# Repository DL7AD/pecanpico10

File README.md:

# Pecan Pico 10 - A lightweight APRS tracker and digipeater
This project contains the Pecan Pico project in it's 10th version. A Pecan is a cheap lightweight APRS position tracker designed especially for small ballons which may fly for months. This tracker has been made in respect of weight, functionality and price because it's usually used once like a satellite. While the balloon can fly for a long time, this tracker is solar powered and recharges it's battery at daytime and uses the power stored in the battery at night.
Since this version the tracker is also able to receive APRS (AFSK and FSK). So it's able to operate as solar enabled digipeater.

The main features are:
- GPS Tracking
- Taking pictures
- APRS receiption and transmission
- Measuring Temperature/Airpressure/Humidity (up to 3 separate sensors)
- Digipeating

__Powering:__ The Pecan Pico 10 can be powered either by USB or by a single LiPO cell which are charged with solar cells. In power safe mode, it uses 50mW and around 150-200mW in normal operation. [dive deeper](powering.md)

__Storage:__ There can be stored up to 14,560 data points (GPS & telemetry) without any external memory devices. For additional storage and picture logging, a Micro SD card can be inserted into the device.

__Transceiver:__ Though the software is mainly optimized for APRS operation, it can be also used for 2/4FSK (RTTY) and OOK (CW) operation. The maximum transmission power is 100mW. While the transceiver has ony a signle LPF, it is only able to operate on one frequency band (either 2m or 70cm). The inductors/capacitors in the schematic are adjusted to the 2m amateur radio band, but with different components it can be used on the 70cm band too. The fastest tested 2FSK transmission speed is 115k2. While the Pecan can transmit AFSK and 2FSK, it is only able to receive AFSK APRS. It is possible to receive 2FSK APRS too, although the software hasn't been implemented yet.

__Image transmission:__ The software makes use of the JPEG compression of the Omnivision OV5640. Although the connector is suitable for some other cameras too, the OV5640 is the only camera which can be used due to the missing HREF pin. The protocol being used for the images transmission is APRS/SSDV. This protocol is fully APRS compatible but needs extra software to be decoded again which is included in this project. Though the camera can do pictures up to 5MP, there is only enough memory available to take XGA pictures (1024x768px).
TODO: Precise description about APRS/SSDV

__Telemetry transmission:__ Since APRS does only allow a ceirtain amount of telemetry fields being transmitted, the complete telemetry is sent as a binary format along with the position transmissions in the comment field. The APRS packet stays completly compatible with the existing network. The additional telemetry can be decoded with an additional decoder which is included in this project. It is the same decoder  which decodes APRS/SSDV too. The software is currently running on [this website](http://www.wlankabel.com).

__Sensors:__ The Pecan uses a single chip (BME280) to measure the temperature, airpressure and humidity. There can be attached up to two additional BME280's for various purposes like internal and external temperatures. You may want to have an external sensor while the internal sensor on the PCB is influenced by the heat generated by the components. The difference can vary between 2 and 10°C.

__Additional sensors:__ The Pecan provides an external busses (I2C and UART) from where addional sensors can be accessed. On the 10a variant is a signle GPIO pin, which can be used for varios stuff. There can either be I2C or UART be used on the 10a variant while I2C shared the same pins as UART does. In the 10b variant the additional GPIO pin has been removed, therefore I2C and UART are now separate. If you have no need for UART/I2C, those pins can be also used as normal GPIO's.

__GNSS (GPS):__ The ublox EVA-7M chip can receive GPS which is used to determine it's location and the region specific APRS frequency. Since the GPS draws a lot of power, it can be switched on and off as needed. The device is also compatible with the ublox EVA-M8 which can receive GLONASS, Beido and Galileo too.

__Debugging/Configuration:__ The device can be accessed over USB (serial terminal) in order to configure it or get debug messages out of the device. The log memory can also be accessed over USB.

__Schematic:__ Here we go! [Download](https://raw.githubusercontent.com/DL7AD/pecanpico10/master/tracker/hardware/pico/output/pecanpico10.pdf)

__Operation variants__
- Car/Balloon Tracker
- Digipeater
- Weather station (software not implemented yet)
- Image transmitting device
All variants can be combined with each other

__Software Manual__
TODO: How to access it through USB
TODO: How to configure the device

__More:__ *Flashing the chip (link missing)*

# Transmitted test pictures

<br>
*Closed Airport Berlin Tempelhof roughly 3km altitude*

<br>
*Picture at low altitude right away after the launch*

<br>
*Clouds somewhere in Germany at an altitude of 12km*

<br>
*Lakes in East Poland (Myślibórz) at 8km altitude, antenna and radar reflector in the picture*

<br>
*South East Berlin (Adlershof/Grünau) taken at roughly 5km altitude*

<br>
*Launch with solar heated balloons (a cooperation with [Aerocene](http://www.aerocene.org))*

Contributions
=============

Please let me know if you have questions or ideas: sven.steudte@gmail.com

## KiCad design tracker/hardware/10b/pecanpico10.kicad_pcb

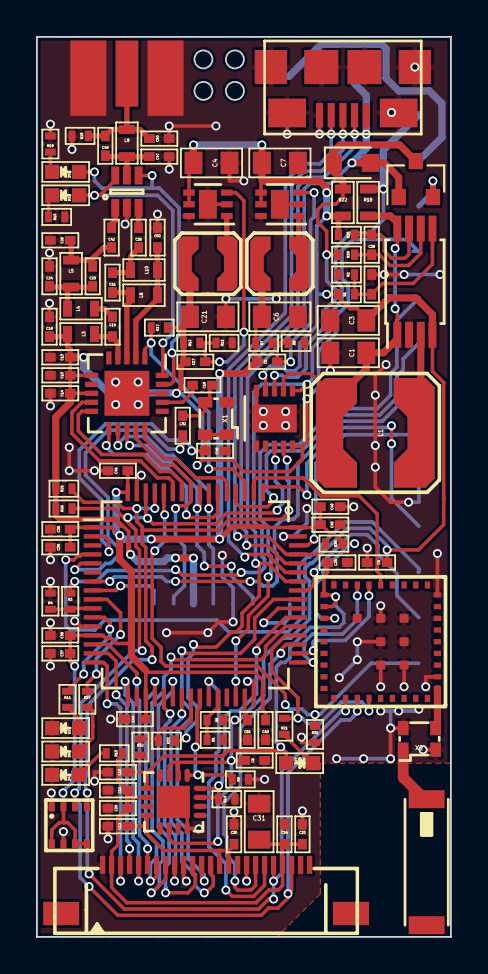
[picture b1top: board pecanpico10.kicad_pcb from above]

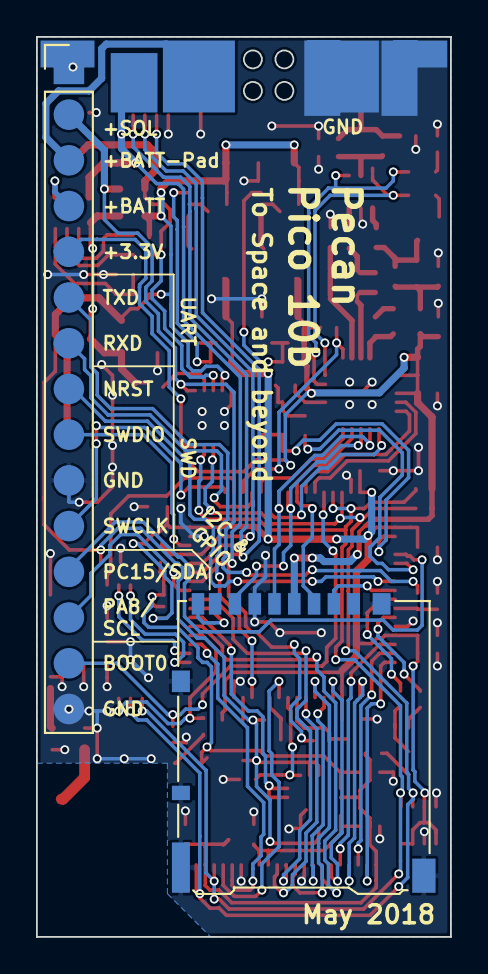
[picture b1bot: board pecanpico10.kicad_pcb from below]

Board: 2 copper layers, 23.0 x 50.0 mm, 119 parts (7 on the bottom side), 93 nets.

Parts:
AE1: 1575AT43A0040E; 575AT43A40
C1, C31: 22u; C_0805
C2: 1n; C_0402
C3, C4, C6, C7, C21: 10u; C_0805
C5, C17, C24, C47, C50: 22p; C_0402
C8, C9, C10, C11, C12, C13, C37, C39, C40, C51: 2u2; C_0402
C14, C20, C29, C30, C33, C35, C43, C44, C45, C46, C48: 100n; C_0402
C15, C16, C34: 100p; C_0402
C18, C19, C36, C42: 470p; C_0402
C25: 3.3p; C_0402
C26: 15p; C_0402
C28: 1u; C_0402
C32, C38: 10n; C_0402
C41: 6.2p; C_0402
C49: 2.2p; C_0402
C52: 12p; C_0402
D1: SDM100K30L-7; D_SOD-323
D2, D7: red; LED_0603
D3, D5: green; LED_0603
D4: yellow; LED_0603
D6: blue; LED_0603
IC1: SPV1040T; TSSOP-8_4.4x3mm_Pitch0.65mm
IC2, IC8: TPS62260DRVR; DFN-6-1EP_2x2mm_Pitch0.65mm
IC3: ADP322ACPZ-115-R7; QFN-16-1EP_3x3mm_Pitch0.5mm
IC4: Si4464-B1B-FM; QFN-20-1EP_4x4mm_Pitch0.5mm
IC5: STM32F413RHT6; LQFP-64_10x10mm_Pitch0.5mm
IC6: EVA-7M or EVA-M8; EVA7M
IC7: PAC1720-1-AIA-TR; DFN-10-1EP_3x3mm_Pitch0.5mm
IC9: BME280
IC10: AS213-92LF; SC-70-6
J1: DM3AT-SF-PEJM5; Hirose_DM3AT-SF-PEJM5
J2: CONN_01X15; Pin_Header_Straight_1x15_Pitch2.54mm
L1: LPS6225-103; LPS6225
L2, L7: LPS3015-222; LPS3015
L3: 470n; R_0603
L4, L9: 56n; R_0603
L5: 82n; R_0603
L8: 220n; R_0603
L10: 150n; R_0603
P1: CONN_01X25; FFC1x24_0.5mm
P3: ZX62-B-5PA(33); USB_Micro-B_SMD
P4: SMA; SMA_EDGE
Q1: FDN306P; SOT-23
R1: 220k; R_0402
R2, R8, R13, R17, R31: 100k; R_0402
R3, R5, R33: 22k; R_0402
R4, R6, R9, R14, R32: 10k; R_0402
R7: 402k; R_0402
R10, R15, R19, R21, R27, R35: 1k5; R_0402
R11, R29, R30: 1k; R_0402
R12: 470k; R_0402
R18, R22: 0R1; R_0603
R20: 1M; R_0402
R25, R26: 4k7; R_0402
W1, W11: Pad; PAD_3x3
W2, W3: Testpad; PAD_3x1.5
W10: Pad; PAD_6x3
X1: KT2016K26000BCW18ZAS; tcxo
X2: SF2316H; tcxo

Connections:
+1V8: C12.1, C30.2, IC3.8, P1.14, P1.15
+3V0: C5.1, C6.1, C35.2, C37.1, C38.1, C39.2, C40.2, C43.2, C44.2, C45.2, C46.2, IC5.1, IC5.13, IC5.19, IC5.32, IC5.48, IC5.64, IC6.21, IC9.2, IC9.5, IC9.6, IC9.8, L2.1, R7.1, R35.1
+3V3: C13.1, C14.1, C15.1, C17.1, C18.1, C21.1, IC4.6, IC4.8, IC7.10, J1.4, J2.5, L3.2, L7.1, R12.1, R17.2, R25.1, R26.1
+BATT: J2.4, Q1.2
+GPS: C10.1, C20.1, D7.2, IC3.5, IC6.19, IC6.20
+SOL: IC7.1, J2.2, R3.1, R18.1
+TCXO: C48.2, IC5.2, X1.1, X1.4
/ADC_VBAT: IC5.27, R5.2, R6.1
/ADC_VSOL: IC5.10, R3.2, R4.1
/ADC_VUSB: IC5.24, R32.1, R33.2
/BOOT0: IC5.60, J2.14, R31.1
/CAM_D2: IC5.14, P1.6
/CAM_D3: IC5.15, P1.4
/CAM_D4: IC5.16, P1.3
/CAM_D5: IC5.17, P1.5
/CAM_D6: IC5.20, P1.7
/CAM_D7: IC5.21, P1.9
/CAM_D8: IC5.22, P1.11
/CAM_D9: IC5.23, P1.13
/CAM_EN: IC3.15, IC3.16, IC5.38, R14.1
/CAM_PCLK: IC5.37, P1.8
/CAM_RESET: IC5.26, P1.19
/CAM_VSYNC: IC5.35, P1.18
/CAM_XCLK: IC5.40, P1.12
/CLOCK_26M: C16.1, C32.1, X1.3
/GPS_EN: IC3.1, IC5.25, R9.1
/GPS_RESET: IC5.50, IC6.14
/GPS_RXD: IC5.33, IC6.16
/GPS_TIMEPULSE: IC5.36, IC6.31, R21.2
/GPS_TXD: IC5.34, IC6.15
/I2C_SCL: IC5.61, IC6.29, IC7.9, IC9.4, P1.20, R25.2
/I2C_SDA: IC5.62, IC6.30, IC7.8, IC9.3, P1.22, R26.2
/IO_LED3: IC5.11, R11.1
/IO_PA8: IC5.41, J2.13
/IO_PC15: IC5.4, J2.12
/IO_RXD: IC5.52, J2.7
/IO_TXD: IC5.29, J2.6
/RADIO_CS: IC4.15, IC5.53
/RADIO_GPIO0: IC4.9, IC5.59
/RADIO_GPIO1: IC4.10, IC5.58
/RADIO_IRQ: IC4.11, IC5.54
/RADIO_RX: D5.2, IC4.19, IC10.4
/RADIO_SDN: IC4.1, IC5.51, R17.1
/RADIO_TX: D2.2, IC4.20, IC10.6
/SD_CS: IC5.8, J1.2
/SD_DET: IC5.39, J1.9
/SENSE_BAT-: C3.1, C4.2, C7.2, C8.1, C9.1, IC1.4, IC2.4, IC2.5, IC3.2, IC3.3, IC3.10, IC7.4, IC8.4, IC8.5, R1.1, R5.1, R22.2, R30.2
/SENSE_SOL: C1.1, IC1.1, IC1.8, IC7.2, L1.2, R18.2
/SPI_MISO: IC4.13, IC5.56, J1.7
/SPI_MOSI: IC4.14, IC5.57, J1.3
/SPI_SCK: IC4.12, IC5.55, J1.5
/SWD_NRST: IC5.7, J2.8
/SWD_SWCLK: IC5.49, J2.11
/SWD_SWDIO: IC5.46, J2.9
/USB_D+: IC5.45, P3.3, R35.2
/USB_D-: IC5.44, P3.2
/USB_ID: IC5.43, P3.4
/USB_VUSB: D1.2, IC5.42, P3.1, Q1.1, R33.1, W1.1
GND: C1.2, C2.2, C3.2, C4.1, C6.2, C7.1, C8.2, C9.2, C10.2, C11.2, C12.2, C13.2, C14.2, C15.2, C18.2, C20.2, C21.2, C24.2, C26.2, C29.1, C30.1, C31.1, C33.1, C34.1, C35.1, C37.2, C38.2, C39.1, C40.1, C43.1, C44.1, C45.1, C46.1, C47.2, C48.1, C50.2, C51.1, C52.1, D3.1, D4.1, D6.1, IC1.2, IC2.2, IC2.6, IC2.7, IC3.12, IC3.17, IC4.18, IC4.21, IC5.12, IC5.18, IC5.31, IC5.47, IC5.63, IC6.2, IC6.7, IC6.9, IC6.18, IC6.37, IC7.5, IC7.6, IC7.11, IC8.2, IC8.6, IC8.7, IC9.1, IC9.7, IC10.2, J1.6, J1.10, J1.11, J2.1, J2.10, J2.15, P1.1, P1.10, P1.17, P1.23, P3.5, P3.6, P4.2, R2.2, R4.2, R6.2, R8.2, R9.2, R10.2, R13.2, R14.2, R19.2, R20.2, R31.2, R32.2, W2.1, W3.1, W10.1, X1.2, X2.2, X2.4
unnamed: AE1.1, X2.1
unnamed: C2.1, IC1.5, R1.2, R2.1
unnamed: C5.2, IC2.3, R7.2, R8.1
unnamed: C16.2, IC4.17
unnamed: C17.2, IC8.3, R12.2, R13.1
unnamed: C19.1, L4.2
unnamed: C19.2, IC4.4, L3.1
unnamed: C24.1, C25.1, L4.1, L5.2
unnamed: C25.2, C26.1, C42.1, L5.1
unnamed: C28.1, IC1.6, R29.1
unnamed: C28.2, IC1.7, R30.1
unnamed: C32.2, IC5.5
unnamed: C36.1, C41.2, L10.2
unnamed: C36.2, IC10.3
unnamed: C41.1, IC4.3, L8.1
unnamed: C42.2, IC10.1
unnamed: C47.1, C49.1, IC10.5, L9.2
unnamed: C49.2, C50.1, L9.1, P4.1, R20.1
unnamed: C51.2, IC5.30
unnamed: C52.2, IC4.2, L8.2, L10.1
unnamed: D2.1, R10.1
unnamed: D3.2, R11.2
unnamed: D4.2, R15.2
unnamed: D5.1, R19.1
unnamed: D6.2, R27.2
unnamed: D7.1, R21.1
unnamed: IC1.3, L1.1
unnamed: IC2.1, L2.2
unnamed: IC5.9, R27.1
unnamed: IC6.1, X2.3
unnamed: IC8.1, L7.2
unnamed: J2.3, W11.1
VDD: D1.1, IC7.3, Q1.3, R22.1, R29.2
VDDA: C11.1, C29.2, C31.2, C33.2, C34.2, IC3.6, P1.2, P1.21, R15.1

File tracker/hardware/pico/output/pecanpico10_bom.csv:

Item,Qty,Reference(s),Value,Footprint,Mouser,Notes,Specs,Price EUR (single at 10pcs),Price EUR (all)
1,1,AE1,GPS-Antenna,,609-1575AT43A0040E,,,0.604,0.604
2,2,"C1, C31",22u,805,,,10V,0.1,0.2
3,10,"C8, C9, C10, C11, C12, C13, C37, C39, C40, C51",2u2,402,,,10V,0.05,0.5
4,13,"C14, C20, C22, C23, C29, C30, C33, C35, C43, C44, C45, C46, C48",100n,402,,,10V,0.02,0.26
5,3,"C15, C16, C34",100p,402,,,10V,0.02,0.06
6,5,"C5, C17, C24, C47, C50",22p,402,,,10V,0.02,0.1
7,4,"C18, C19, C36, C42",470p,402,,,16V,0.02,0.08
8,1,C2,1n,402,,,16V,0.02,0.02
9,5,"C3, C4, C6, C7, C21",10u,805,,,10V,0.07,0.35
10,1,C25,3.3p,402,,,16V,0.02,0.02
11,1,C26,15p,402,,,10V,0.02,0.02
12,1,C27,N/A,402,,do not assemble,16V,0,0
13,1,C28,1u,402,,,10V,0.05,0.05
14,2,"C32, C38",10n,402,,,10V,0.02,0.04
15,1,C41,6.2p,402,,,16V,0.02,0.02
16,1,C49,2.2p,402,,,16V,0.02,0.02
17,1,C52,12p,402,,,16V,0.02,0.02
18,1,D1,SDM100K30L-7,SOD-323,621-SDM100K30L-7,,,0.303,0.303
19,2,"D2, D7",red,603,,,,0.25,0.5
20,2,"D3, D5",green,603,,,,0.25,0.5
21,1,D4,yellow,603,,,,0.25,0.25
22,1,D6,blue,603,,,,0.25,0.25
23,1,IC1,SPV1040T,TSSOP-8,511-SPV1040T,,,2.21,2.21
24,1,IC10,AS213-92LF,SO-70-6,873-AS213-92LF,,,0.635,0.635
25,2,"IC2, IC8",TPS62260DRVR,DFN6,595-TPS62260DRVR,,,0.976,1.952
26,1,IC3,ADP322ACPZ-115-R7,QFN16,584-ADP322ACPZ-115R7,,,1.12,1.12
27,1,IC4,Si4464-B1B-FM,QFN20,634-SI4464-B1X-FMR,,,2.67,2.67
28,1,IC5,STM32F413RHT6,LQFP64,511-STM32F413RHT6,,,8,8
29,1,IC6,EVA-7M or EVA-M8,,672-1000-1-ND (Digikey),,,23.54,23.54
30,1,IC7,PAC1720-1-AIA-TR,DFN10,579-PAC1720-1-AIA-TR,,,0.984,0.984
31,1,IC9,BME280,,262-BME280,,,4.9,4.9
32,1,J1,DM3AT-SF-PEJM5,,798-DM3AT-SF-PEJM5,,,1.91,1.91
33,1,J2,CONN_01X15,100mil,,do not assemble,,0,0
34,1,L1,LPS6225-103,,994-LPS6225-103MRC,,,1.49,1.49
35,1,L10,150n,603,994-0603CS-R15XJLW,,,0.881,0.881
36,2,"L2, L7",LPS3015-222,,994-LPS3015-222MRC,,,0.97,1.94
37,1,L3,470n,603,810-MLJ1608WR47KT000,,,0.172,0.172
38,2,"L4, L9",56n,603,994-0603CS-56NXJLW,,,0.881,1.762
39,1,L5,82n,603,994-0603CS-82NXJLW,,,0.881,0.881
40,1,L6,0R,603,,fit 0R instead of L,,0.02,0.02
41,1,L8,220n,603,994-0603CS-R22XJLW,,,0.881,0.881
42,1,P1,CONN_01X25,,,included with camera,,0,0
43,1,P3,ZX62-B-5PA(33),,798-ZX62-B-5PA33,,,0.5,0.5
44,1,P4,SMA Connector,,,,,1,1
45,1,Q1,FDN306P,SOT-23,512-FDN306P,,,0.28,0.28
46,1,R1,220k,402,,,1%,0.02,0.02
47,6,"R10, R15, R19, R21, R27, R35",1k5,402,,,1%,0.02,0.12
48,3,"R11, R29, R30",1k,402,,,1%,0.02,0.06
49,1,R12,470k,402,,,1%,0.02,0.02
50,5,"R2, R8, R13, R17, R31",100k,402,,,1%,0.02,0.1
51,6,"R4, R6, R9, R14, R16, R32",10k,402,,,1%,0.02,0.12
52,2,"R18, R22",0R1,603,667-ERJ-3RSFR10V,,,0.155,0.31
53,1,R20,1M,402,,,1%,0.02,0.02
54,2,"R25, R26",4k7,402,,,1%,0.02,0.04
55,3,"R3, R5, R33",22k,402,,,1%,0.02,0.06
56,1,R7,402k,402,,,1%,0.02,0.02
57,1,X1,KT2016K26000BCW18ZAS,,581-KT2016K2BCW18ZAS,,,1.45,1.45
58,1,Camera,,,,,,10,10
59,1,Assembly,,,,,,20,20
60,1,PCB,,,,,,3,3
,,,,,,,,,97.235

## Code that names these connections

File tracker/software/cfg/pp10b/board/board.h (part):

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/*
 * GPIOA setup:
 *
 * PA0  - CAM_D2                    (input pulldown).
 * PA1  - CAM_D3                    (input pulldown).
 * PA2  - CAM_D4                    (input pulldown).
 * PA3  - CAM_D5                    (input pulldown).
 * PA4  - CAM_D6                    (input pulldown).
 * PA5  - CAM_D7                    (input pulldown).
 * PA6  - CAM_D8                    (input pulldown).
 * PA7  - CAM_D9                    (input pulldown).
 * PA8  - IO_PA8                    (input floating).
 * PA9  - USB_VBUS                  (input pulldown).
 * PA10 - USB_ID                    (alternate 10).
 * PA11 - USB_DM                    (alternate 10).
 * PA12 - USB_DP                    (alternate 10).
 * PA13 - SWDIO                     (alternate 0).
 * PA14 - SWCLK                     (alternate 0).
 * PA15 - GPS_EN                    (input pulldown).
 */
#define VAL_GPIOA_MODER             (PIN_MODE_INPUT(GPIOA_PIN0) |           \
                                     PIN_MODE_INPUT(GPIOA_PIN1) |           \
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/*
 * GPIOB setup:
 *
 * PB0  - CAM_RESET                 (input pulldown).
 * PB1  - ADC_VBAT                  (input pulldown).
 * PB2  - BOOT1                     (input pulldown).
 * PB3  - SPI_SCK                   (input pulldown).
 * PB4  - SPI_MISO                  (input pulldown).
 * PB5  - SPI_MOSI                  (input pulldown).
 * PB6  - RADIO_GPIO1               (input pulldown).
 * PB7  - RADIO_GPIO0               (input pulldown).
 * PB8  - I2C_SCL                   (input pulldown).
 * PB9  - I2C_SDA                   (input pulldown).
 * PB10 - IO_TXD                    (input floating).
 * PB11 - PIN11                     (input pulldown).
 * PB12 - GPS_RXD                   (input pulldown).
 * PB13 - GPS_TXD                   (input pulldown).
 * PB14 - GPS_RESET                 (input pulldown).
 * PB15 - GPS_TIMEPULSE             (input pulldown).
 */
#define VAL_GPIOB_MODER             (PIN_MODE_INPUT(GPIOB_PIN0) |           \
                                     PIN_MODE_INPUT(GPIOB_PIN1) |           \
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/*
 * GPIOC setup:
 *
 * PC0  - SD_CS                     (output pushpull highspeed high).
 * PC1  - IO_BLUE                   (input pulldown).
 * PC2  - ADC_VSOL                  (input pulldown).
 * PC3  - IO_GREEN                  (input pulldown).
 * PC4  - ADC_VUSB                  (input pulldown).
 * PC5  - CAM_VSYNC                 (input pulldown).
 * PC6  - CAM_PCLK                  (input pulldown).
 * PC7  - CAM_EN                    (input pulldown).
 * PC8  - SD_DET                    (input pullup verylowspeed).
 * PC9  - CAM_XCLK                  (input pulldown).
 * PC10 - RADIO_SDN                 (input pullup verylowspeed).
 * PC11 - IO_RXD                    (input floating).
 * PC12 - RADIO_CS                  (output pushpull high).
 * PC13 - TCXO_EN                   (input pulldown).
 * PC14 - OSC32_IN                  (input floating).
 * PC15 - OSC32_OUT                 (input floating).
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 *
 * PD0  - PIN0                      (input pulldown).
 * PD1  - PIN1                      (input pulldown).
 * PD2  - RADIO_IRQ                 (input pulldown).
 * PD3  - PIN3                      (input pulldown).
 * PD4  - PIN4                      (input pulldown).
 * PD5  - PIN5                      (input pulldown).
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
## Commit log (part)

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2018-03-01 Removed linefeeds
2018-03-02 Minor formatting fix to debug messages.
2018-03-02 Expand encoding selectors in radio manager. Revise SPI in 446x.c
2018-03-03 Abort packet TX when 446x transmit start fails.
2018-03-03 corrected some typos
2018-03-04 Update config when flash is not valid or config.c has changed.
2018-03-04 WIP on HDLC flag sending by 446x.
2018-03-06 Implement timeout for 446x not exiting TX state.
2018-03-06 WIP adding radio channel and step size options.
2018-03-07 Improve bad packet handling. Was consuming all output buffers.
2018-03-07 Expand command table to include radio step and chan.
2018-03-08 Implemented packet TX via packet system radio manager queue.
2018-03-09 Quick fix for 446x.c temperature reading. Refactoring opportunity.
2018-03-10 Edit typo
2018-03-11 Created 10b hardware files
2018-03-13 Added I2C clock stretching timeout
2018-03-14 Rework to support test project build.
2018-03-15 Move regex into pkt/sys.
2018-03-17 Work in progress for FSK encoding.
2018-03-21 Fixed minor compilation error
2018-03-22 Added trace level
2018-03-24 Add -D default for trace level. Trace command w/o param lists level.
2018-03-26 Initial TX FSK implemented. Relatively untested ATM.
2018-03-29 Fix error in sense of packet open. Tidy up in 446x driver.
2018-03-30 Fix I2C interfering with image capture (was not locked).
2018-04-01 Turned off some checking and measuring options in chconf.h
2018-04-04 Enable CCM use for buffers, aprs messages to pos callsigns. Dummy GPS.
2018-04-05 Fix memory leak in TX. Add 'heap' command. Minor refactoring & docs.
2018-04-07 Improved mem command.
2018-04-07 Revert CCM heap to normal. Speed up burst send TX. Increase exc. stack.
2018-04-08 Increase exception stack even more. Minor tidy ups.
2018-04-12 Update to ChibiOS trunk rev 119i2.
2018-04-15 Fixed coordinate format error
2018-04-16 Fixed USB/battery isolation bug, increased schottky diode pad size
2018-04-17 Relabeled pinheader
2018-04-17 Small fix to ?aprsh command.
2018-04-19 Fixed reload bug, added new chart
2018-04-19 Tidy up
2018-04-22 Add default APRS frequency
    - Include freq param in config.c
    - modify frequency setting in 446x.c
    - modify frequency calc in pktradio.c
2018-04-27 Multiple changes.
    - Update APRS position packet to include timestamp.
    - Add ability to set air pressure level to control GPS airborne mode
    - Add capability for time only acquisition from GPS when fixed coord set
    - Revise GPIO naming to use IO1 - IO3 (2 & only if not external BME)
2018-04-28 Refactor GPS dynamic model configuration.
2018-04-29 Added 2m bandpass trap filter in GPS rx Removed unnecessary resistor Edited/Added schematic comments
2018-04-30 Added SAW Filter Optimized Antenna connections Created SAW Filter pad
2018-05-02 Moved wires around, added vias, created GERBERs for 10b
2018-05-03 Restructure config APRS and DIGI settings/layout
2018-05-08 Update ChibiOS to rev 12014 (now includes F413 in official code base)
2018-05-12 Update to dynamic frequency selection.
2018-05-13 Fix POS thread TX frequency and identity.
2018-05-13 Fix incorrect frequency for blind send after change of frequency.
2018-05-13 Changed message format for decoder
2018-05-14 Improve APRS trace messages. Fix BCN not reporting from LOG pos'n.
2018-05-21 Include openocd config into cfg folder. Update gitignore.
2018-05-21 Updated build configuration for Mac Eclipse.
2018-05-25 Rationalise GPIO LED configuration.
2018-06-08 Work in progress...
    - Enable make for PP10b
    - Update PP10b board.h and portab
    - Some work on moving POS -> BCN to merge them
2018-06-13 Revise APRS IO bits handling. Changes supporting rev B complete.
    - IO1 to IO4 now reported in telemetry regardless of board rev.
    - IO1 to IO4 accepted in APRS command but no effect if not configured.
2018-06-15 Updated PWM buffering release.
    - Enabled for PP10A using CCM based buffers.
2018-06-19 Revise GPS fallback data to utilise log entry position.
2018-06-20 Implemented callsign validation
2018-06-22 Complete implementation of common beacon service for POS and DIGI.
2018-06-22 Revise GPS polling timing and Telemetry cycle timing.
2018-06-23 Fix time stamp for fixed GPS.
2018-06-24 CCM related changes...
    - Revise CMM heap allocation to use .ram4 linker defined region
    - Deprecate code to use CCM pool based AX25 TX buffers
2018-06-26 Changes...
    - Implement ?aprsp so that it runs a one time beacon thread
    - Enable ?aprsp to respond from the profile of the rx call sign
2018-06-28 Fixed GPS UART implementation
2018-06-28 Improve handling of low battery and init error condition for GPS.
2018-07-01 Added new power scheme
2018-07-02 Additional changes to reduce core memory footprint...
    - Reduce thread WA sizes for beacon and collector
    - Move beacon WA to CCM
    - Move AFSK decoder WA into CCM
    - Fix APRS PARAM list string sizes
2018-07-04 Multiple changes:
    - WIP LLD functions for abstraction of radio interfaces
    - Add new string output functions for GPS states and model
    - Trim WA size for image thread
    - Further tidy up in AFSK decoder
2018-07-08 Move all GPIO definitions in portab.h
2018-07-11 Remove duplicate const declaration in ssdv.c
2018-07-17 Multiple changes:
    - Rework packet system event codes
    - Revise radio manager to support pending changes to 446x driver
    - Minor updates to documentation
    - WIP update 446x driver to dynamically configure 4464/4463 chip
2018-07-21 Implement dynamic Si446x chip identification.
    - Patch is applied if 4463 detected
    - Register settings differ if 4463 detected
    - Added 'radio' command in CLI to list radio data
    - Patches to ChibiOS (also in trunk)
    - Update of SPI settings halconf.h to match latest ChibiOS
    - Move assert for invalid radio in common function
2018-07-29 Added more charts
2018-07-31 Multi-radio capability implemented in 446x driver.
2018-08-04 Multiple changes...
    - More work on radio HAL/LLD
    - Geofence and default frequency rework
    - Fix 446x exception halt on TX timeout
    - Further rework of portab files
2018-08-06 Clear aged GPS data if GPS not started due low volts.
2018-08-08 Updates:
    - Set config.c example of using POS for DIGI beacon
    - Collector waits 60S max for GPS fix before giving result
    - New datapoint with state GPS_TIME is written when RTC is first set
2018-08-10 Changes:
    - Deprecate EXTI from mcuconf.h
    - Move setting out of pktconf.c and deprecate it
    - New status codes and diagnostics added to AFSK decoder
    - Revise allocation packet service and AFSK driver structures
    - Revise 446x conditional initialisation placement
2018-08-12 Switch "no camera" image to interlaced. SSDV can't handle progressive.
2018-08-12 Renamed folder math to tools
2018-08-13 WIP implementing DSP data as dynamic versus static.
2018-08-15 Complete refactoring of AFSK DSP code base.
2018-08-15 Reimplemented debug on UART again
2018-08-16 Revise beacon/collector to emit a trackpoint on startup.
2018-08-18 Improved locking mechanism in decoder
2018-08-18 Added more performance to image insertion
2018-08-18 Multiple changes:
    - Add further buffer overrun checks in ax25 & digipeater code
    - TRACE message updates in aprs.c
    - Allow image.c to encode images while TX active
    - Enable image.c to have 2 TX sessions outstanding
    - Fix DMA overrun bug in ov5640.c (camera h/w fault induced)
    - Update SWD probe configuration so hard reset works
2018-08-19 Updated SSDV
2018-08-20 Switch to DMA SBM for image capture. Limit is 64K buffer for now.
2018-08-22 Switch to SBM DMA image capture.
    - Still some infrequent issue with DBM to be debugged
    - Limit capture to 64K image for now
2018-08-23 Add further memory asserts and rework PWM queue handling
2018-08-30 Move collector thread WA up to 2K
2018-09-02 RX service changes:
    - Implement sub-state for RX to reduce complexity
    - Allow queued packet RX decode to complete during TX
    - Deprecate RX locking code in ov5640 handler
    - Rename some functions to better reflect their operation
2018-09-06 Rewrite of console/USB handler WIP.
    - Refactor console state machine.
    - Fix OS event handler bug.
    - Patch USB Serial event broadcast to stop event flooding
2018-09-09 Console USB updates:
    - Add conditional TRACE #define
    - Increase USB buffers in halconf to 4 from 2
    - Add assert in USB serial drive to catch invalid buffer state
    - Minor updates to hal_buffers
    - Reduce exception stack by 2K since prior increase was for testing
    - Type fix in usbcfg.c
2018-09-14 Updates:
    - Correct some misuse of systime_t and syinterval_t
    - Rework RX in progress wait to use events
    - Fix some mixed definitions for the packetHandlerData struct
    - Add .no_burst option for IMG app packet send
    - Remove retry loop in ov5640.c (duplicated functionality in image.c)
    - Remove RX state setting in pktStopDecoder(...)
2018-09-19 Changes:
    - Test implementation of GPS power saving mode
    - Update OTG so support of 5 endpoints available
    - Implement SDU2 serial over USB channel
    - Consolidate pkt system initialization under one function
2018-09-22 Added KiCAD library files
2018-09-24 Interim changes to image ID for SSDV.
    - Image ID 0 - 127 for even # reset
    - Image ID 128 - 255 for odd # reset
2018-09-25 Moved serial module import This has been done so that the module must not be installed if not needed
2018-09-28 Changes:
    - Rework image reject handling.
    - Rework image packet re-send handling.
    - Rework driver references (I2C, etc.)
    - Fix wrong trace message in 4460 2FSK send thread
2018-09-30 Updates:
    - image command and python script rolled in from webcam_dev branch
    - further WIP on SSDV buffer full handling (more to do)
2018-09-30 Lock I2C during PDCMI DMA phase
2018-10-04 Updates:
    - Specify timeouts in sysinterval in ublox.c
    - Minor documentation updates
2018-10-08 Updates:
    - Fix serial ID not incremented when timestamping RTC set
    - Rework GPS power on logic.
    - Prepare for dynamic console port switch capability
    - Add define for second SDU references
2018-10-11 Added zoom options to OV5640 driver
2018-10-12 Improve digipeat TRACE. Improve PWM diagnostics.
2018-10-25 Implement GPS disciplined TCXO measurement.
    - Currently TCXO measurement is operational
    - si446x clock update from updated TCXO currently disabled.
    - si446x TX clock update works but RX is not working right.
2018-10-28 WIP refactoring of 446x driver, pktradio, pktservice.
2018-11-05 WIP radio Manager, move many TRACE_INFO to TRACE _DEBUG
2018-11-10 Continuing work on Radio Manager, packet buffers, etc.
    - Implemented improved callback capability
    - Implemented guarded pool for RX buffers
    - Update function parameters in 446x
    - minor changes to tcxo service
    - improve RSSI capture handling
    - defer allocation of packet buffer in afsk until opening HDLC
2018-11-17 Fix buffer overrun in packet print. Add conditional to 446x.
2018-11-21 De-clutter serial IO. Fix console to work with UART & USB based serial.
2018-12-29 Fix #define logic for DISABLE_HW_WATCHDOG
2019-01-04 Adjust MCO div for 96MHz SYSCLK
2019-01-07 Improved HDLC bit sync strategy.
2019-01-13 Updates:
    - update 4463 register settings to improve rx performance
    - deprecate some conditional code settings
    - reorganising portab.h #defines
2019-02-03 Adding further checks for error conditions in 446x driver.
2019-02-18 Updates:
    - further rationalisation of portab utilisation
    - improve 446x driver handling of limited GPIO connections
2019-02-28 Add documentation to serial mux. Rework EOT event monitor.
2019-03-19 Updates:
    - WIP on generalising serial mux driver implementation
    - Refactor GPS driver UBX protocol handling
    - Implement full CRC checking in UBLOX driver
    - Geofence now returns default for ROW
    - WIP on updating ADC driver to use MCU factory calibration
    - Update 446x driver to check for SPI fault on init/wake up
2019-05-19 Fixes and changes:
    - Fix burst packet bug in 446x.c
    - Remove redundant change in image.c
    - Move packet release code into pktservice.c/h
    - Rename service functions
    - Revise make handling of FPU configuration

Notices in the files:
tracker/software/cfg/pp10b/board/board.h:
ChibiOS - Copyright (C) 2006..2016 Giovanni Di Sirio
Licensed under the Apache License, Version 2.0 (the "License");
